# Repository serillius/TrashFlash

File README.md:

View this project on [CADLAB.io](https://cadlab.io/project/28978). 

# TrashFlash

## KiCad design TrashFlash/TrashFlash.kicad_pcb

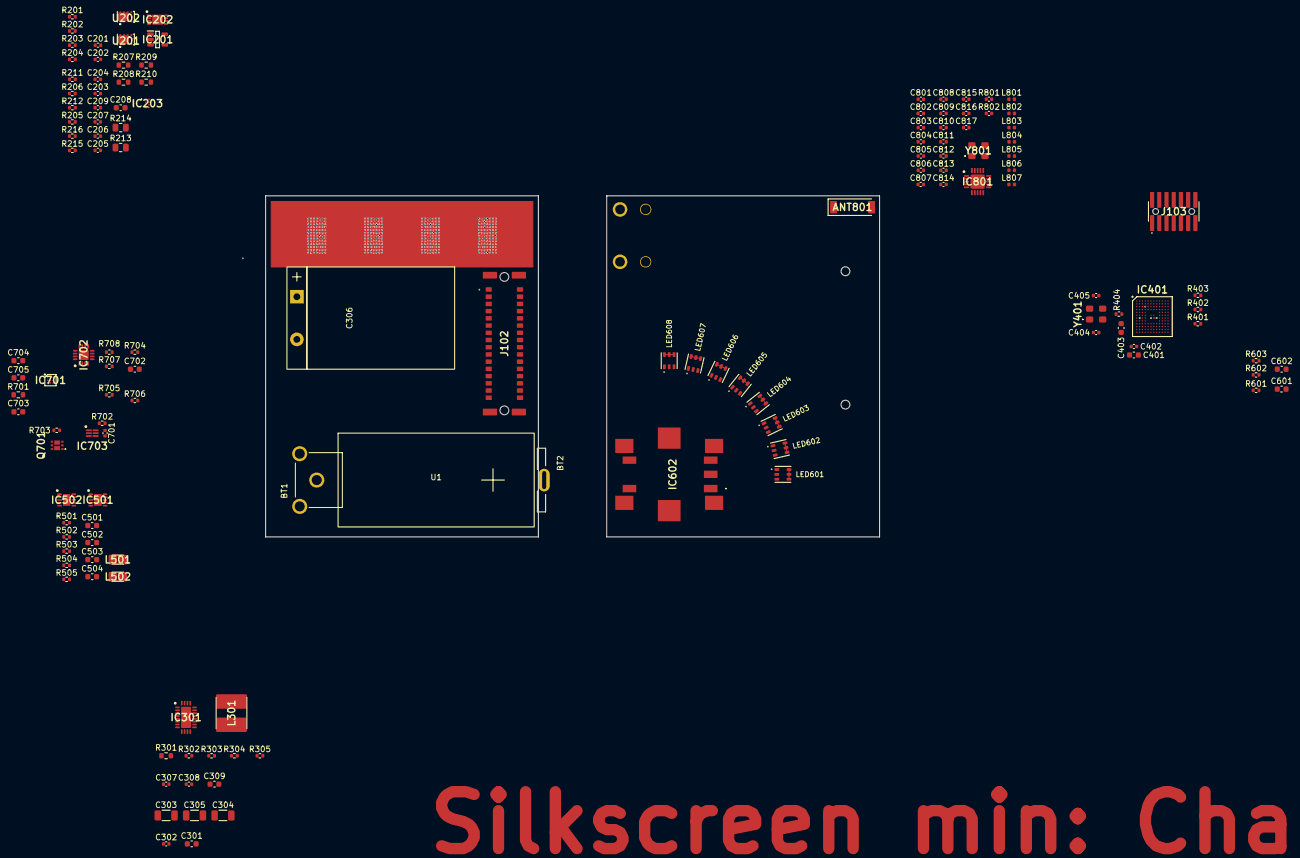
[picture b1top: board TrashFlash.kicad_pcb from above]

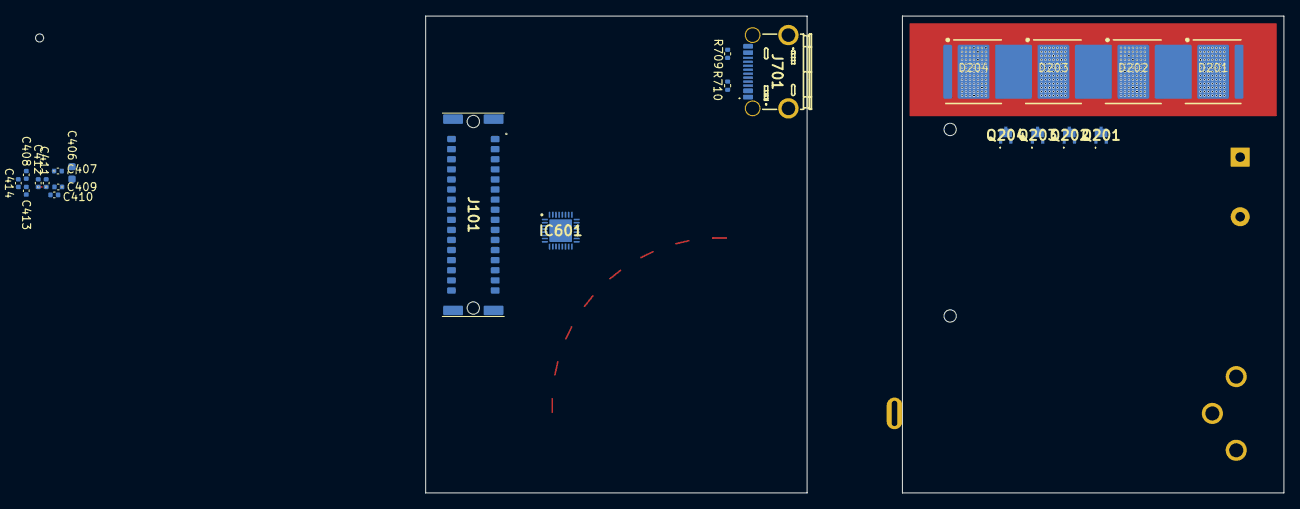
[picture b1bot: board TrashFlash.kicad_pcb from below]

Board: 6 copper layers, 108.0 x 60.0 mm, 157 parts (22 on the bottom side), 125 nets.

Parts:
ANT801: 0868AT43A0020001E; ANTC7020X90N
BT1: 628; BAT_628
BT2: 5223; BAT_5223
C201, C202, C803, C810: 100p; C_0402_1005Metric
C203, C204, C308: 22p; C_0402_1005Metric
C205, C206, C207, C209, C302, C407, C408, C409, C410, C411, C412, C413, C414, C701, C811, C817: 100n; C_0402_1005Metric
C208, C401, C403, C601, C602, C705: 1u; C_0603_1608Metric
C301, C309, C406, C703, C704: 4.7u; C_0603_1608Metric
C303, C304, C305: 10u; C_1206_3216Metric
C306: UBY1V392MHL6TN; CP_Radial_D16.0mm_P7.50mm
C307: 470p; C_0402_1005Metric
C402, C814, C816: 10n; C_0402_1005Metric
C404, C405: 6.8p; C_0402_1005Metric
C501, C503: 10u; C_0603_1608Metric
C502, C504: 22u; C_0603_1608Metric
C702: 2.2u; C_0603_1608Metric
C801, C804: 1.5p; C_0402_1005Metric
C802: 1p; C_0402_1005Metric
C805: 3.3p; C_0402_1005Metric
C806: 3.9p; C_0402_1005Metric
C807: 0.3p; C_0402_1005Metric
C808, C809: 10p; C_0402_1005Metric
C812, C813, C815: 220p; C_0402_1005Metric
D201, D202, D203, D204: XFL05K
IC201: AD8615AUJZ-REEL; SOT95P280X100-5N
IC202: ADG5419BCPZ-RL7; SON50P300X200X80-9N-D
IC203: SN74LXC2T45QDTTRQ1
IC301: LTC3643IUDD#PBF; QFN50P300X500X80-25N-D
IC401: STM32L471QEI6; BGA132C50P12X12_700X700X60
IC501, IC502: TPS63900DSKR; SON50P250X250X80-11N-D
IC601: LP5024RSMR; QFN40P400X400X100-33N-D
IC602: PEC11S-929K-S0015; PEC11S929KS0015
IC701: BQ27426YZFR; BGA9C50P3X3_158X162X62
IC702: BQ24230RGTR; QFN50P300X300X100-17N-D
IC703: BQ29732DSER; SON50P150X150X80-6N
IC801: CC110LRGPR; QFN50P400X400X100-21N-D
J101: 15130322601000
J102: 15230322601000
J103: FTSH-107-01-L-DV-K-A; FTSH-107-XX-YYY-DV-K-A
J701: USB4800-03-A; USB480003A
L301: 74438367068; INDPM5454X310N
L501, L502: 74438343022; INDM2016X100N
L801, L803, L804, L806: 12n; L_0402_1005Metric
L802, L805, L807: 18n; L_0402_1005Metric
LED601, LED602, LED603, LED604, LED605, LED606, LED607, LED608: 150282M153310
Q201, Q202, Q203, Q204: BC56-10PA,115; PTVS24VZ1UPAZ
Q701: PMDPB30XNAX
R201, R203, R205, R212: 100k; R_0402_1005Metric
R202, R204, R709, R710: 5.1k; R_0402_1005Metric
R206, R211: 10k; R_0402_1005Metric
R207, R208, R209, R210: 68m; R_0603_1608Metric
R213: 10m; R_0805_2012Metric
R214: 1; R_0805_2012Metric
R215, R216, R401, R402, R403, R404: 1k; R_0402_1005Metric
R301: 25m; R_0603_1608Metric
R302: 560k; R_0402_1005Metric
R303: 56k; R_0402_1005Metric
R304, R603: 12k; R_0402_1005Metric
R305: 400k; R_0402_1005Metric
R501: 511; R_0402_1005Metric
R502: 6.49k; R_0402_1005Metric
R503: 0; R_0402_1005Metric
R504: 8.25k; R_0402_1005Metric
R505: 36.5k; R_0402_1005Metric
R601, R602, R703, R704, R705: 2.2k; R_0402_1005Metric
R701: 10m; R_0603_1608Metric
R702: 330; R_0402_1005Metric
R706: 33K; R_0402_1005Metric
R707: 1.8K; R_0402_1005Metric
R708: 10K; R_0402_1005Metric
R801: 330; C_0402_1005Metric
R802: 56k; C_0402_1005Metric
U1: CR123A
U201, U202: SI5448DU-T1-GE3; SI5448DUT1GE3
Y401: ECS-160-8-33B2-CTN-TR3; ECS160833B2CTNTR3
Y801: ECS-260-10-33B-CKM-TR; ECS160833B2CTNTR3

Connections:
+5V: C206.1, C208.2, C209.2, C504.1, IC201.5 (V+), IC203.8 (VCCB), IC502.6 (VOUT), J101.A14, J101.B14, J102.A14, J102.B14, LED601.4 (A_BLUE), LED601.5 (A_GREEN), LED601.6 (A_RED), LED602.4 (A_BLUE), LED602.5 (A_GREEN), LED602.6 (A_RED), LED603.4 (A_BLUE), LED603.5 (A_GREEN), LED603.6 (A_RED), LED604.4 (A_BLUE), LED604.5 (A_GREEN), LED604.6 (A_RED), LED605.4 (A_BLUE), LED605.5 (A_GREEN), LED605.6 (A_RED), LED606.4 (A_BLUE), LED606.5 (A_GREEN), LED606.6 (A_RED), LED607.4 (A_BLUE), LED607.5 (A_GREEN), LED607.6 (A_RED), LED608.4 (A_BLUE), LED608.5 (A_GREEN), LED608.6 (A_RED)
+BATT: BT2.P1, IC701.C1 (SRP), IC701.C3 (BAT), R701.1, R702.1
-BATT: BT1.N1, BT1.N2, BT1.N3, C701.2, IC703.4 (VSS), Q701.1
/Battery_Management/BAT_CHARGER_INOUT: C703.1, IC701.C2 (SRN), IC702.2 (BAT_1), IC702.3 (BAT_2), R701.2
/Battery_Management/BIN: IC701.B1 (BIN), J102.A8
/Battery_Management/COUT: IC703.2 (COUT), Q701.5
/Battery_Management/DOUT: IC703.3 (DOUT), Q701.2
/Battery_Management/GPOUT: IC701.A1 (GPOUT), J102.B8
/Battery_Management/ISET_CHG: IC702.16 (ISET), R707.1
/Battery_Management/SCL: IC701.A3 (SCL), J102.A9, R705.2
/Battery_Management/SDA: IC701.A2 (SDA), J102.B9, R704.2
/Battery_Management/TMR_CHG: IC702.14 (TMR), R706.1
/Battery_Management/TS_CHG: IC702.1 (TS), R708.1
/Battery_Management/V-_PROT: IC703.6 (V-), R703.1
/Battery_Management/VCC_PROT: C701.1, IC703.5 (BAT), R702.2
/Battery_Management/~CHG: IC702.9 (~CHG), J102.A10
/Battery_Management/~PGOOD: IC702.7 (~PGOOD), J102.B10
/CC1: J701.A5 (CC1), R710.1
/CC2: J701.B5 (CC2), R709.1
/LED_Current_Source/EN_LED_RANGE_20A: IC203.2 (A1), J102.A4
/LED_Current_Source/EN_LED_RANGE_200mA: IC203.3 (A2), J102.B4
/LED_Current_Source/GATE_DRV_20A: IC203.7 (B1), R215.1
/LED_Current_Source/GATE_DRV_200mA: IC203.6 (B2), R216.1
/LED_Current_Source/LED_TP: D201.TP, D202.TP, D203.TP, D204.TP
/LED_Current_Source/SELECT_LED_RANGE: IC202.6 (IN), J102.A5
/LED_Current_Source/TCA_BASE_DRIVE: C204.1, IC201.1, Q201.1 (B), Q202.1 (B), Q203.1 (B), Q204.1 (B)
/LED_Current_Source/TCA_COLLECTOR: D204.1 (K), Q201.3 (C), Q202.3 (C), Q203.3 (C), Q204.3 (C), R203.2
/LED_Current_Source/TCA_CURRENT_FB: C203.1, IC202.1 (D), R206.1
/LED_Current_Source/TCA_EMITTER: R207.2, R208.2, R209.2, R210.2, R211.2, R213.1, R214.1
/LED_Current_Source/TCA_FB_20A: IC202.8 (SB), R213.2, U201.1
/LED_Current_Source/TCA_FB_200mA: IC202.2 (SA), R214.2, U202.1
/LED_Current_Source/TCA_NEG_IN: C204.2, IC201.4 (-), R211.1, R212.2
/LED_Current_Source/TCA_POS_IN: C203.2, IC201.3 (+), R205.2, R206.2
/LED_Current_Source/VMEAS_VDRIVE: C201.1, J102.A6, R201.1, R202.2
/LED_Current_Source/VMEAS_VLED: C202.1, J102.B6, R203.1, R204.2
/LED_Current_Source/VSET_LED_CURRENT: J102.B5, R205.1
/LED_Supply/BOOST_DRV: C302.2, IC301.15 (BOOST)
/LED_Supply/EN_LED_DRIVE_BOOST: IC301.7 (RUN), J102.A2
/LED_Supply/FBCAP: IC301.9 (FBCAP), R302.1, R303.1, R304.2
/LED_Supply/ILIM_DRV: C309.1, IC301.14 (INTVCC), IC301.21 (ILIM)
/LED_Supply/INDIS_DRV: IC301.16 (INDIS_1), IC301.17 (INDIS_2), L301.1
/LED_Supply/LED_DRIVE_CAPACITOR_CHARGED: IC301.11 (CAPGD), J102.B2
/LED_Supply/SW_DRV: C302.1, IC301.18 (SW_1), IC301.19 (SW_2), IC301.20 (SW_3), L301.2
/LED_Supply/VIN_DRV: C301.1, IC301.4 (VIN_1), IC301.5 (VIN_2), R301.2
/LED_Supply/VSET_LED_DRIVE_VOLTAGE: J102.A3, R303.2
/LED_Supply/~LED_DRIVE_INPUT_POWER_FAIL: IC301.12 (PFO), J102.B3
/MCU/BOOT0: IC401.H2 (NRST), R401.1, R403.2
/MCU/NRST: IC401.A4 (BOOT0), R402.1
/MCU/SCL_USER_INTERFACE: IC601.29 (SCL), R602.2
/MCU/SDA_USER_INTERFACE: IC601.28 (SDA), R601.2
/MCU/USB_DN: J701.A7 (DN1), J701.B7 (DN2)
/MCU/USB_DP: J701.A6 (DP1), J701.B6 (DP2)
/MCU/VREF: C403.1, IC401.L1 (VREF+)
/Supply/CFG1_5V: IC502.3 (CFG1), R505.1
/Supply/CFG1_VDD: IC501.3 (CFG1), R502.1
/Supply/CFG2_5V: IC502.4 (CFG2), R504.1
/Supply/CFG2_VDD: IC501.4 (CFG2), R501.1
/Supply/CFG3_5V: IC502.5 (CFG3), R503.1
/Supply/EN_5V_REG: IC502.1 (EN), J102.A7
/Supply/LX1_5V: IC502.9 (LX1), L502.1
/Supply/LX1_VDD: IC501.9 (LX1), L501.1
/Supply/LX2_5V: IC502.7 (LX2), L502.2
/Supply/LX2_VDD: IC501.7 (LX2), L501.2
/User_Interface/BLUE0: IC601.3 (OUT2), LED601.3 (K_BLUE)
/User_Interface/BLUE1: IC601.6 (OUT5), LED602.3 (K_BLUE)
/User_Interface/BLUE2: IC601.9 (OUT8), LED603.3 (K_BLUE)
/User_Interface/BLUE3: IC601.12 (OUT11), LED604.3 (K_BLUE)
/User_Interface/BLUE4: IC601.15 (OUT14), LED605.3 (K_BLUE)
/User_Interface/BLUE5: IC601.18 (OUT17), LED606.3 (K_BLUE)
/User_Interface/BLUE6: IC601.21 (OUT20), LED607.3 (K_BLUE)
/User_Interface/BLUE7: IC601.24 (OUT23), LED608.3 (K_BLUE)
/User_Interface/GREEN0: IC601.2 (OUT1), LED601.2 (K_GREEN)
/User_Interface/GREEN1: IC601.5 (OUT4), LED602.2 (K_GREEN)
/User_Interface/GREEN2: IC601.8 (OUT7), LED603.2 (K_GREEN)
/User_Interface/GREEN3: IC601.11 (OUT10), LED604.2 (K_GREEN)
/User_Interface/GREEN4: IC601.14 (OUT13), LED605.2 (K_GREEN)
/User_Interface/GREEN5: IC601.17 (OUT16), LED606.2 (K_GREEN)
/User_Interface/GREEN6: IC601.20 (OUT19), LED607.2 (K_GREEN)
/User_Interface/GREEN7: IC601.23 (OUT22), LED608.2 (K_GREEN)
/User_Interface/IREF_RGB: IC601.31 (IREF), R603.1
/User_Interface/RED0: IC601.1 (OUT0), LED601.1 (K_RED)
/User_Interface/RED1: IC601.4 (OUT3), LED602.1 (K_RED)
/User_Interface/RED2: IC601.7 (OUT6), LED603.1 (K_RED)
/User_Interface/RED3: IC601.10 (OUT9), LED604.1 (K_RED)
/User_Interface/RED4: IC601.13 (OUT12), LED605.1 (K_RED)
/User_Interface/RED5: IC601.16 (OUT15), LED606.1 (K_RED)
/User_Interface/RED6: IC601.19 (OUT18), LED607.1 (K_RED)
/User_Interface/RED7: IC601.22 (OUT21), LED608.1 (K_RED)
/User_Interface/VCAP_RGB: C602.1, IC601.32 (VCAP)
GND: C201.2, C202.2, C205.2, C206.2, C207.2, C208.1, C209.1, C301.2, C303.2, C304.2, C305.2, C306.2, C308.2, C309.2, C401.2, C402.2, C403.2, C404.2, C405.2, C406.2, C407.2, C408.2, C409.2, C410.2, C411.2, C412.2, C413.2, C414.2, C501.2, C502.2, C503.2, C504.2, C601.2, C602.2, C702.2, C703.2, C704.2, C705.2, C801.1, C805.2, C806.1, C807.1, C808.2, C809.2, C810.2, C811.2, C812.2, C813.2, C814.2, C815.2, C816.2, C817.2, IC201.2 (V-), IC202.3 (GND), IC202.7 (VSS), IC202.9 (EP), IC203.4 (GND), IC301.1 (PGND_1), IC301.2 (PGND_2), IC301.25 (SGND), IC401.D3 (VSS_1), IC401.E3 (VSS_2), IC401.F2 (VSS_3), IC401.F6 (VSS_4), IC401.F7 (VSS_5), IC401.F11 (VSS_6), IC401.F12 (VSS_7), IC401.J1 (VSSA/VREF-), IC501.5 (CFG3), IC501.8 (GND), IC501.11 (TP), IC502.8 (GND), IC502.11 (TP), IC601.25 (ADDR0), IC601.26 (ADDR1), IC601.33 (GND), IC602.C1 (C), IC602.E1 (E), IC701.B2 (VSS), IC702.4 (~CE), IC702.5 (EN2), IC702.8 (VSS), IC702.15 (TD), IC702.17 (TP), IC801.16 (GND_1), IC801.19 (GND_2), IC801.21 (GND_3), J101.A1, J101.A16, J101.B1, J101.B16, J102.A1, J102.A16, J102.B1, J102.B16, J103.5, J103.7, J103.11, J701.A1 (GND_1), J701.A12 (GND_2), J701.MH3, J701.MH4, J701.MH5, J701.MH6, Q701.4, R202.1, R204.1, R212.1, R304.1, R305.1, R403.1, R501.2, R502.2, R503.2, R504.2, R505.2, R603.2, R703.2, R706.2, R707.2, R708.2, R709.2, R710.2, R802.2, U201.2, U202.2, Y401.2 (GND), Y401.4 (GND), Y801.2 (GND), Y801.4 (GND)
unnamed: ANT801.1 (FEED), C807.2, L805.1
unnamed: C307.2, R305.2
unnamed: C801.2, C802.1, L801.1, L802.2
unnamed: C802.2, C804.1, L806.1, L807.1
unnamed: C803.1, L804.1
unnamed: C803.2, C806.2, L805.2
unnamed: C804.2, L802.1, L803.2
unnamed: C805.1, L803.1, L804.2
unnamed: C810.1, L807.2
unnamed: D201.1 (K), D202.2 (A)
unnamed: D202.1 (K), D203.2 (A)
unnamed: D203.1 (K), D204.2 (A)
unnamed: C307.1, C308.1, IC301.10 (ITH)
unnamed: C405.1, IC401.F1 (PH0-OSC_IN), Y401.3 (OUT/IN)
unnamed: IC401.G1 (PH1-_OSC_OUT), R404.1
unnamed: C702.1, IC701.B3 (VDD)
unnamed: C811.1, IC801.5 (DCOUPL)
unnamed: IC801.17 (RBIAS), R802.1
unnamed: IC801.13 (RF_N), L801.2
unnamed: IC801.12 (RF_P), L806.2
unnamed: C809.1, IC801.8 (XOSC_Q1), Y801.3 (OUT/IN)
unnamed: IC801.10 (XOSC_Q2), R801.2
unnamed: Q201.2 (E), R207.1
unnamed: Q202.2 (E), R208.1
unnamed: Q203.2 (E), R209.1
unnamed: Q204.2 (E), R210.1
unnamed: Q701.3, Q701.6
unnamed: R215.2, U201.3
unnamed: R216.2, U202.3
unnamed: C404.1, R404.2, Y401.1 (IN/OUT)
unnamed: C808.1, R801.1, Y801.1 (IN/OUT)
VBUS: C705.1, IC702.13 (IN), J101.A13, J101.B13, J102.A13, J102.B13, J701.A4 (VBUS_1), J701.A9 (VBUS_2)
VDD: C207.1, C401.1, C402.1, C406.1, C407.1, C408.1, C409.1, C410.1, C411.1, C412.1, C413.1, C414.1, C502.1, C601.1, C812.1, C813.1, C814.1, C815.1, C816.1, C817.1, IC202.5 (EN), IC203.1 (VCCA), IC203.5 (DIR), IC401.C4 (VDD_1), IC401.C11 (VDD_2), IC401.E2 (VBAT), IC401.G2 (VDD_3), IC401.G6 (VDD_4), IC401.G7 (VDDIO2), IC401.G11 (VDD_5), IC401.G12 (VDD_6), IC401.H3 (VDD_7), IC401.M1 (VDDA), IC501.6 (VOUT), IC601.27 (VCC), IC801.4 (DVDD), IC801.9 (AVDD_1), IC801.11 (AVDD_2), IC801.14 (AVDD_3), IC801.15 (AVDD_4), IC801.18 (DGUARD), J101.A15, J101.B15, J102.A15, J102.B15, J103.3, R401.2, R402.2, R601.1, R602.1, R704.1, R705.1
VSYS: C501.1, C503.1, C704.1, IC301.8 (FBSYS), IC301.13 (PFI), IC301.24 (CLP), IC501.1 (EN), IC501.2 (SEL), IC501.10 (VIN), IC502.2 (SEL), IC502.10 (VIN), IC702.6 (EN1), IC702.10 (OUT_1), IC702.11 (OUT_2), R301.1
Vdrive: C205.1, C303.1, C304.1, C305.1, C306.1, D201.2 (A), IC202.4 (VDD), IC301.3 (CAP), R201.2, R302.2

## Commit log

2025-03-21 Backlink to CADLAB.io has been added.
2025-03-23 Added Parts
2025-03-24 started LED schematic
2025-03-24 Removed old file
2025-03-26 Added 3D model
2025-03-30 Bevor new Shematic
2025-03-31 Started redrawing shematic
2025-03-31 LED_Current_Source.kicad_sch redesigne
2025-04-01 Cleaned up LED_Current_Source schematic
2025-04-05 Added Power Supply
2025-04-05 Changed LP5024 symbol
2025-04-05 Added RGB leds/driver for user interface
2025-04-05 Added comment
2025-04-06 Changed SI51448 Footprint
2025-04-06 Added gitignore and removed temp files
2025-04-06 Added Battery Management
2025-04-06 Added USB and powernets
2025-04-06 Rotary encoder added + 3D stuff
2025-04-07 Footprints 3D model fixed
2025-04-09 3d models and footprints
2025-04-11 Added Crystal to library
2025-04-11 Added STM32L471 symbol to lib
2025-04-11 Added STM32L471 footprint to lib
2025-04-11 Added STM32 to schematic
2025-04-12 Added power supply to STM32
2025-04-12 Changed the layout of MCU schematic
2025-04-12 Added netlabels / cleaned up schematic
2025-04-13 Added 3D-models to footprints, PCB outline and component placement
2025-04-23 Added Wireless and inter PCB connector
2025-04-23 Old changes
2025-04-23 Added battery and connectors to PCB
2025-04-23 Stackup changed, Led placement adjusted
2025-04-23 Moved USB and added JTAG connector
2025-04-24 Added Caps to Battery Charger
2025-04-29 LED via stitch und han gmerkt das ich usversehe d batterie im letschte kommit use gno han sorry :)
2025-05-06 Added battery and connectors, Schematic remark for BQ297xx
2025-05-06 Some layout suggestions
